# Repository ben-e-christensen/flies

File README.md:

# FLIES — electrometer + camera acquisition and analysis

Scripts for the FLIES charging experiments in the Burton Lab. A Keithley 6514
electrometer logs charge (or current/voltage) over serial while FLIR
Grasshopper3 and/or Logitech Brio 101 cameras record the sample. An Arduino
relay switches two lamps (A = "going into Faraday cage", B = "going into
acrylic"). When the signal "blips", the scripts save a camera burst around it.
The other scripts plot, review, turn into video, and compress the resulting
session folders.

Split out of [burtonlab](https://github.com/ben-e-christensen/burtonlab)
(`flies/` folder) with its git history kept.

## Setup

```bash
python -m venv .venv
.venv\Scripts\activate
pip install numpy matplotlib opencv-python pyserial pillow pandas
```

You also need:

- **PySpin** (Spinnaker SDK) for the FLIR camera. Install the wheel that
  matches your Python version from Teledyne FLIR's site. This is why the old
  `.venv312` existed.
- **ffmpeg / ffprobe** for the Brio capture, the video scripts and the
  compressor. Several scripts hard-code an `FFMPEG = r'...'` path in their
  CONFIG block, so check it.
- Set the instrument serial ports in **`coms.py`**.

Most scripts have a `# ============ CONFIG ============` block at the top, and
many default to paths like `E:\Ben Christensen\FLIES\...`. Edit it before you
run a script, or pass a session folder on the command line.

## A session folder

The acquisition scripts write one folder per run:

```
session_<YYYY-MM-DD_HH-MM-SS>/
    meta.txt                 key<TAB>value settings (cap_F, fps, ports, wall_clock_start ...)
    electrometer.csv         time,charge,trigger  |  time,voltage_V,trigger (voltage mode)
    events.csv               one row per blip / manual save (event,time,lamp,...)
    lamps.csv                lamp state over time (newer sessions only)
    flir/e001_0000.png ...   FLIR burst frames for event 1 (16-bit PNG)
    flir_frames.csv          time,event,filename
    brio1/e001_0000.jpg ...  Brio burst frames (+ brio1_frames.csv)
    *_cont/p003_000000.*     continuous frames during lamp phase 3 (some modes)
    analysis/                written by the analysis scripts
```

All timestamps are seconds since the Start button, on one shared clock, so the
CSVs line up with each other.

---

## Top-level files

### Shared config

| File | What it does |
|---|---|
| `coms.py` | The one place for serial ports. `port('keithley')` / `port('arduino')` returns the right `COMx` on Windows or `/dev/tty*` on Linux. Every acquisition script imports it. |

### Acquisition (Tkinter GUIs: live plot, lamp buttons, Start/Stop)

| File | What it does |
|---|---|
| `main.py` | Charge-mode Keithley + **one FLIR**, with automated lamps. Start runs the cycle: lamp A on → wait for a charge blip → lamp stays on 30 s → dark → lamp B → … . The FLIR keeps a RAM ring buffer and writes it to disk only when a blip fires, so each burst includes the lead-in. Pressing a manual lamp button turns the automation off. (The docstring still says "UNTESTED", but the commit history says it has been tested.) |
| `main_untested.py` | Same automation with **two FLIRs**. Only the camera opposite the lit lamp caches. The blip rule is a swing in either direction, and each burst includes 15 s of post-roll after the blip. |
| `main_test.py` | Dual-FLIR version from `main_untested.py`, plus **continuous 20 fps saving** from camera A while one lamp (`CONT_LAMP`) is on. Frames go to `flir_a_cont/p###_######.png` through a bounded writer pool. When the disk can't keep up, frames are dropped and counted so RAM doesn't fill. |
| `main_voltage.py` | The newest and largest version. The Keithley runs in **voltage mode** across a 1 nF cap (1 mV = 1 pC), with one FLIR (PySpin) and two Brio 101s (read through ffmpeg for real MJPG). Each lamp has its own settings for which cameras cache and which save continuously. It adds an "Auto trigger" toggle and a "Save burst" button (or the M key). Writes to `E:\Ben Christensen\FLIES\session_*`. |

### Session analysis and plotting

| File | What it does |
|---|---|
| `plot_main.py` | Plots charge for a whole session (`electrometer.csv`). Events show as dashed lines and FLIR burst spans as cyan bands. Saves `session_charge.png`. Works with charge-mode and voltage-mode data (Q = C·V, with C from `meta.txt`). |
| `plot_blips.py` | One plot per event, covering ±30 s around the blip. A second x-axis shows FLIR frame numbers and shades the burst span. |
| `session_overview.py` | Whole-session overview plus one plot per **episode** (events close together are merged). Colors come from the lamp state logged in `events.csv` / `lamps.csv`. Writes `analysis/overview/`. Pass a session folder, or the FLIES folder to process every session. |
| `session_overview_multiple.py` | One long charge plot across several sessions or folders, ordered by `wall_clock_start`. Sessions are either laid end to end or placed at their real clock times. Writes PNG, SVG (for Inkscape) and a sessions CSV. |
| `logger.py` | Despite the name, this is the interactive **blip viewer**. It shows the session trace, a zoom on the current event, and the Brio frame nearest the cursor. Events come from `events.csv`, your own `EXTRA_TIMES` and optional offline detection. Keyboard controls: n/p for events, arrow keys to step frames, space to play, s to take a snapshot, e to export. `--export` writes summary PNGs without opening the window. |

### Video making

| File | What it does |
|---|---|
| `flir_video.py` | Makes one MP4 per event from the FLIR burst frames (`e001_*.png` …), with the 16-bit frames scaled to 8-bit. |
| `video_and_charge.py` | Event video. Every camera that recorded the event is on top (FLIR, brio1, brio2), and the charge trace draws itself in underneath. The FLIR sets the clock. The other cameras show their latest frame at or before that time, labeled with the offset. Also writes a `_sync.csv` that maps each video frame to its source files. |
| `video_cont.py` | Same as `video_and_charge.py`, for sessions where the Brios saved **continuous** frames (`brio*_cont/`) instead of bursts. |
| `triple.py` | An older 3-panel version for one FLIR + one Brio: FLIR burst, Brio burst and charge trace side by side, with a sync CSV. |
| `trying.py` | Side-by-side clip of Brio continuous frames and a charge trace that draws itself in, for frame ranges you list in `CLIPS` (e.g. `p002_001550` → `p002_001560`). Supports slow motion. |

### Frame quality check

| File | What it does |
|---|---|
| `fly_finder.py` | Scans every continuous FLIR frame (`flir_a_cont/p###_######.png`) and compares it with a reference frame using mean diff, fraction of changed pixels, sharpness and brightness. It flags robust outliers. The scan can resume where it stopped. Writes `scores.csv`, `flagged.csv`, a plot and copies of flagged frames to `frame_check/`. |
| `flag.py` | Summarizes the results from `fly_finder.py`: counts by reason, by session and lamp phase, runs of consecutive flagged frames, the most extreme frames, and missing files. It can copy the worst N frames per metric so you can look through them. |
| `prune.py` | One-off: removes rows at or before a given reference frame from `scores.csv`, plus rows whose files no longer exist. Keeps a `.bak` copy. The paths are hard-coded. |

### Data transfer

| File | What it does |
|---|---|
| `compress.py` | Copies a FLIES folder for transfer, turning each image sequence into one video (H.264, or FFV1 for exact 16-bit) with a per-frame manifest CSV. Other files are copied as-is, and the source folder is never modified. Frame counts are checked with ffprobe, and the script can resume. `--restore` / `--extract` decode videos back into the original frame files. |
| `compress_v2.py` | `compress.py` plus lock files so several runs can go at once, and `--skip-cont`, `--only-cont` and `--reverse` for ordering. Each run writes its own log. |

---

## `other_modes/` — earlier acquisition variants

These put the repo root on `sys.path` so they can import `coms`. Output goes to
`other_modes/Kiethley_data/`.

| File | What it does |
|---|---|
| `main.py` | Minimal GUI: Keithley in **charge** mode, live scrolling plot, CSV log. No cameras, no relay. |
| `main_ubuntu.py` | The same minimal GUI in **current** mode (nA), with serial auto-detection for Linux `/dev/ttyUSB*` / `ttyACM*`. |
| `main_test.py` | Charge mode + **two Brio 101s** captured through ffmpeg (real MJPG). JPEGs are written as received, with no re-encode. |
| `main_current.py` | **Current** mode + two Brios (ffmpeg) + FLIR (PySpin). Charge is recovered afterwards by integrating the current. |
| `main_voltage.py` | **Voltage** mode across an RC network (R = 5.15 MΩ, C = 93.4 nF), with charge computed live as Q = C·V. Two Brios through OpenCV + FLIR. |
| `Kiethley_data/electrometer_2026-09-01_17-08-18.csv` | A small sample charge log (`time,charge` in coulombs). |

## `test_scripts/` — hardware tests and early prototypes

| File | What it does |
|---|---|
| `cam_test.py` | Opens one webcam with OpenCV/DSHOW and shows it live. q quits. |
| `cam_test_v2.py` | Records two Brios with ffmpeg and a live preview. SPACE starts or stops recording. `list` shows the dshow device names. |
| `pair_test.py` | Measures the real fps of two cameras by counting only frames whose content changed, because `grab()` on DSHOW returns True even when no new frame arrived. |
| `electro.py` | Headless Keithley charge logging for `DURATION_S` seconds, then a plot. No GUI. |
| `integrate.py` | Integrates a current-mode `electrometer.csv` (trapezoid rule) into charge. Writes `charge_integrated.csv` and a two-panel plot. |
| `integrated.py` | Early GUI: Keithley charge + two OpenCV webcams. |
| `old_main.py` | Earlier current-mode Keithley + two Brios (OpenCV) + FLIR logger, with charge integrated live. |
| `main_arduino.py` | `old_main.py` plus Arduino relay control of the lamps. `main.py` at the top level was built from this. |
| `main_no_cam.py` | Keithley charge mode + Arduino relay buttons, no cameras. |
| `plot_main.py` | Plots a single `electrometer.csv` (charge in pC). By default it uses the newest one. |
| `plot_blocks.py` | Splits a charge log at `SPLIT_TIMES` into labeled blocks (Idle / Fan On / Beads In …). Each block gets its own plot, an optional fit, and optional 10 s zoom windows. |
| `spike_review.py` | Finds charge spikes (|dq/dt| outliers) in a time window, copies the camera frames around each one and makes a movie of the block. |
| `make_clip.py` | Makes an MP4 of cam0/cam1 frames between `CLIP_START` and `CLIP_END`, per camera and side by side. |
| `identity_test.png` | Test image. |

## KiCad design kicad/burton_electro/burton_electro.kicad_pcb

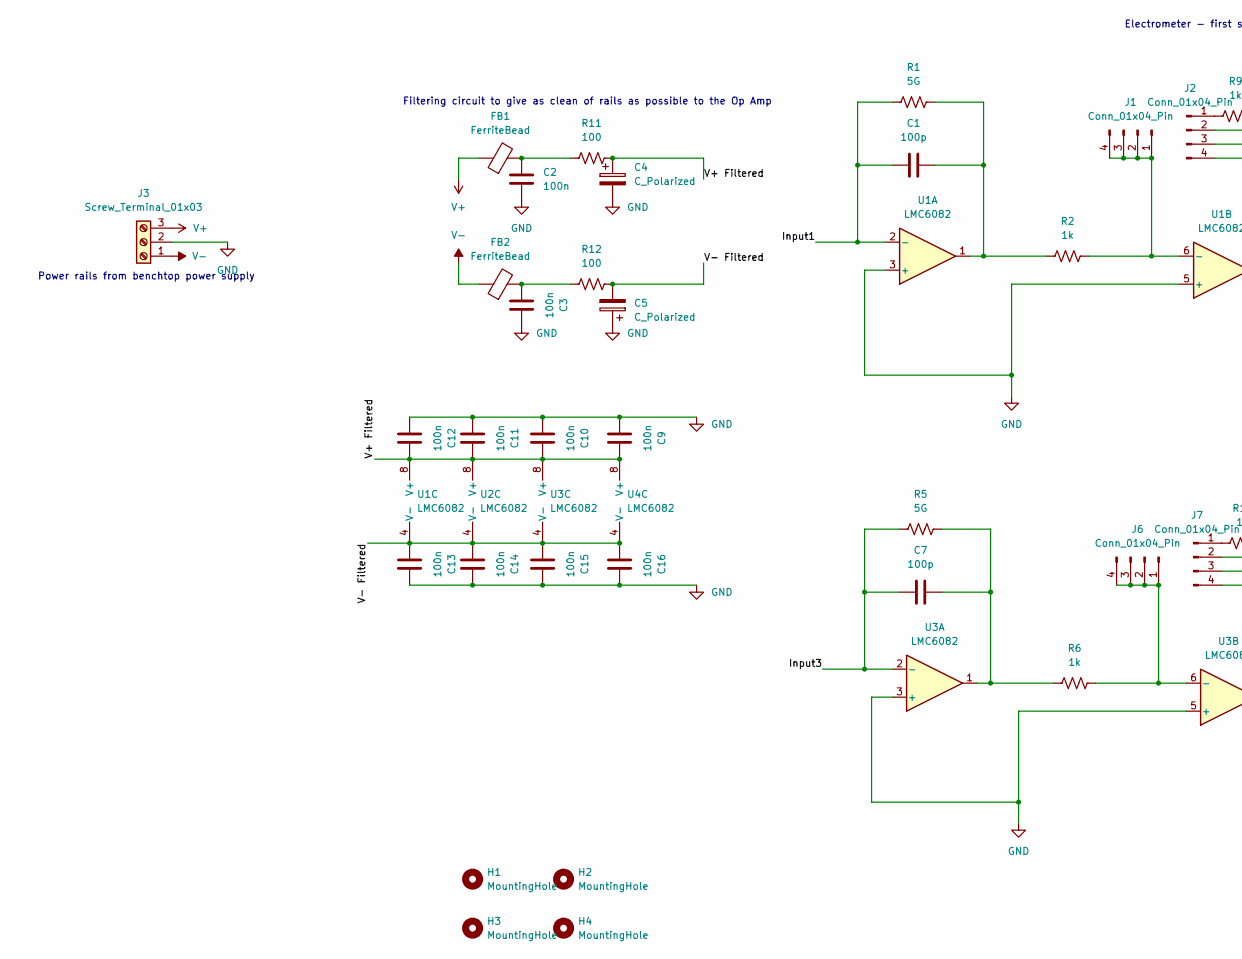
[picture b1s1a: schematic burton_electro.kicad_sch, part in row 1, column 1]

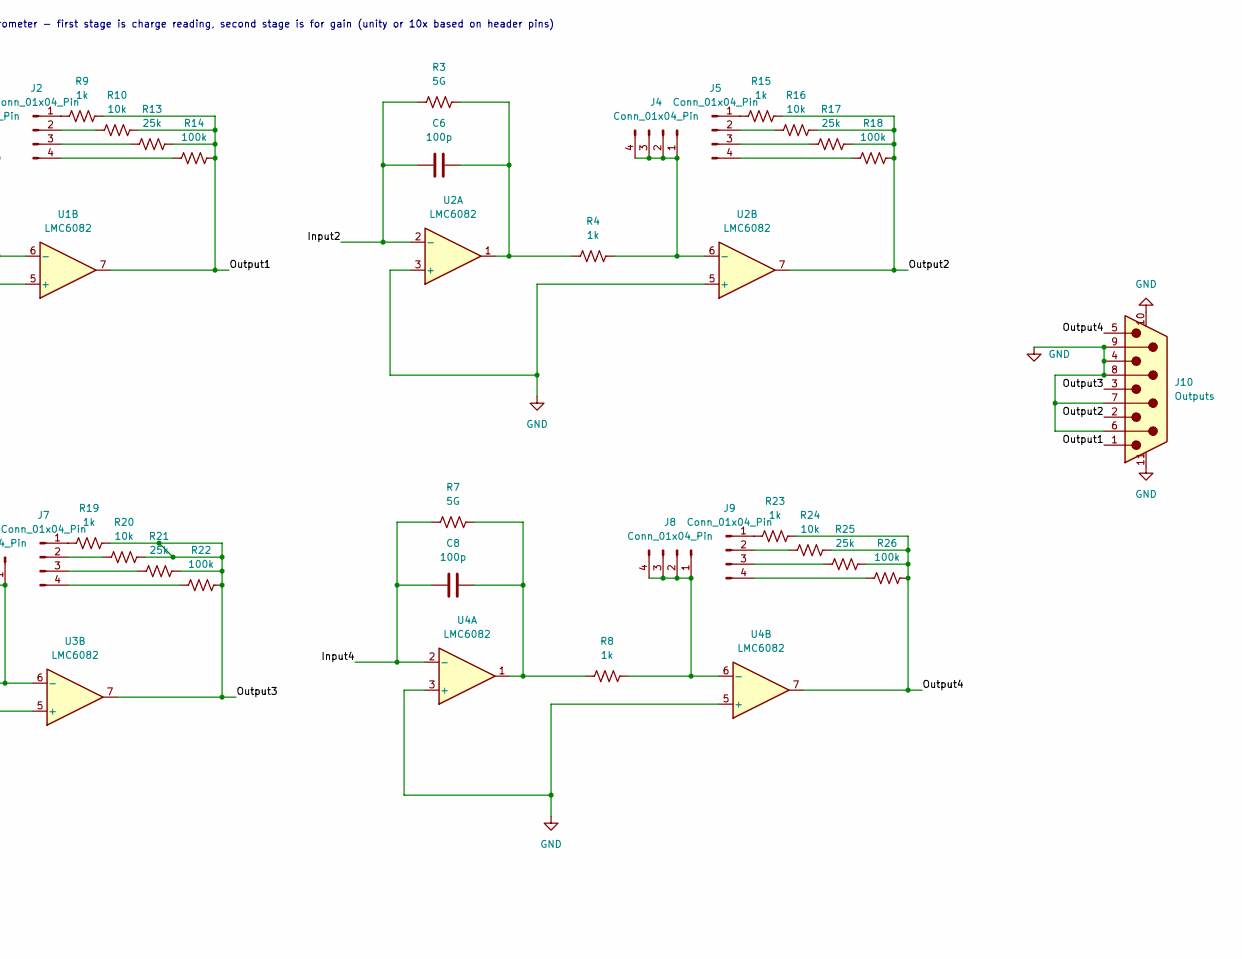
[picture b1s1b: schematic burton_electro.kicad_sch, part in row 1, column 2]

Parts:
C1, C6, C7, C8: 100p; C_Disc_D3.0mm_W1.6mm_P2.50mm
C2, C3, C9, C10, C11, C12, C13, C14, C15, C16: 100n; C_0805_2012Metric_Pad1.18x1.45mm_HandSolder
C4, C5: C_Polarized; CP_Elec_10x10.5
FB1, FB2: FerriteBead; L_1206_3216Metric
H1, H2, H3, H4: MountingHole; MountingHole_2.7mm
J1, J2, J4, J5, J6, J7, J8, J9: Conn_01x04_Pin; PinHeader_1x04_P2.54mm_Vertical
J3: Screw_Terminal_01x03; Altech_AK100_1x03_P5.00mm
J10: Outputs; DSUB-9_Pins_Horizontal_P2.77x2.84mm_EdgePinOffset7.70mm_Hou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
R1, R3, R5, R7: 5G; R_Axial_DIN0204_L3.6mm_D1.6mm_P2.54mm_Vertical
R2, R4, R6, R8, R9, R15, R19, R23: 1k; R_0805_2012Metric_Pad1.20x1.40mm_HandSolder
R10, R16, R20, R24: 10k; R_0805_2012Metric_Pad1.20x1.40mm_HandSolder
R11, R12: 100; R_0805_2012Metric_Pad1.20x1.40mm_HandSolder
R13, R17, R21, R25: 25k; R_0805_2012Metric_Pad1.20x1.40mm_HandSolder
R14, R18, R22, R26: 100k; R_0805_2012Metric_Pad1.20x1.40mm_HandSolder
U1, U2, U3, U4: LMC6082; DIP-8_W7.62mm

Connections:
/Input1: C1.1, R1.1, U1.2 (-)
/Input2: C6.1, R3.1, U2.2 (-)
/Input3: C7.1, R5.1, U3.2 (-)
/Input4: C8.1, R7.1, U4.2 (-)
/Output1: J10.1, R9.2, R10.2, R13.2, R14.2, U1.7
/Output2: J10.2, R15.2, R16.2, R17.2, R18.2, U2.7
/Output3: J10.3, R19.2, R20.2, R21.2, R22.2, U3.7
/Output4: J10.5, R23.2, R24.2, R25.2, R26.2, U4.7
/V+ Filtered: C4.1, C9.2, C10.2, C11.2, C12.2, R11.2, U1.8 (V+), U2.8 (V+), U3.8 (V+), U4.8 (V+)
/V- Filtered: C5.2, C13.1, C14.1, C15.1, C16.1, R12.2, U1.4 (V-), U2.4 (V-), U3.4 (V-), U4.4 (V-)
GND: C2.1, C3.2, C4.2, C5.1, C9.1, C10.1, C11.1, C12.1, C13.2, C14.2, C15.2, C16.2, J3.2, J10.4, J10.6, J10.7, J10.8, J10.9, J10.10, J10.11, J10.SH, U1.3 (+), U1.5 (+), U2.3 (+), U2.5 (+), U3.3 (+), U3.5 (+), U4.3 (+), U4.5 (+)
unnamed: C1.2, R1.2, R2.1, U1.1
unnamed: C2.2, FB1.2, R11.1
unnamed: C3.1, FB2.2, R12.1
unnamed: C6.2, R3.2, R4.1, U2.1
unnamed: C7.2, R5.2, R6.1, U3.1
unnamed: C8.2, R7.2, R8.1, U4.1
unnamed: J1.1, J1.2, J1.3, J1.4, R2.2, U1.6 (-)
unnamed: J2.1, R9.1
unnamed: J2.2, R10.1
unnamed: J2.3, R13.1
unnamed: J2.4, R14.1
unnamed: J4.1, J4.2, J4.3, J4.4, R4.2, U2.6 (-)
unnamed: J5.1, R15.1
unnamed: J5.2, R16.1
unnamed: J5.3, R17.1
unnamed: J5.4, R18.1
unnamed: J6.1, J6.2, J6.3, J6.4, R6.2, U3.6 (-)
unnamed: J7.1, R19.1
unnamed: J7.2, R20.1
unnamed: J7.3, R21.1
unnamed: J7.4, R22.1
unnamed: J8.1, J8.2, J8.3, J8.4, R8.2, U4.6 (-)
unnamed: J9.1, R23.1
unnamed: J9.2, R24.1
unnamed: J9.3, R25.1
unnamed: J9.4, R26.1
V+: FB1.1, J3.3
V-: FB2.1, J3.1

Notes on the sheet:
Electrometer - first stage is charge reading, second stage is for gain (unity or 10x based on header pins)
Power rails from benchtop power supply
Filtering circuit to give as clean of rails as possible to the Op Amp

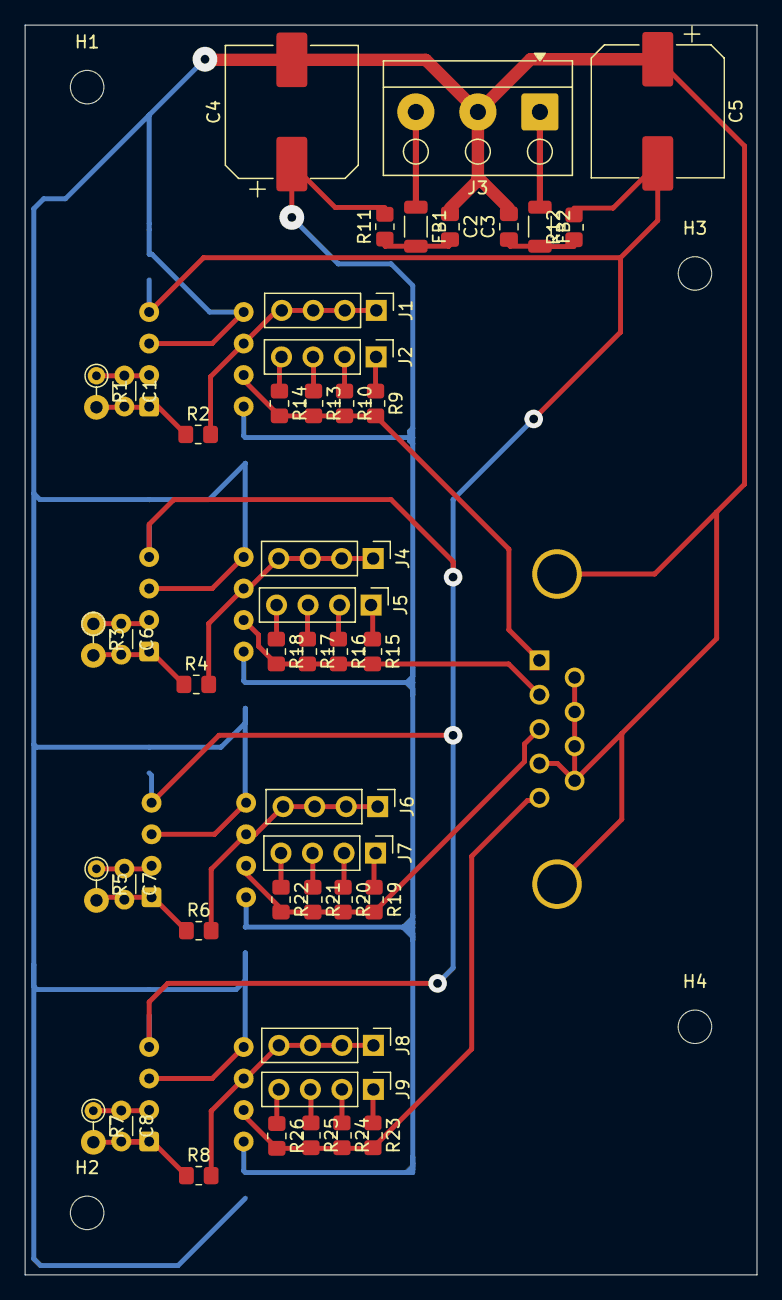
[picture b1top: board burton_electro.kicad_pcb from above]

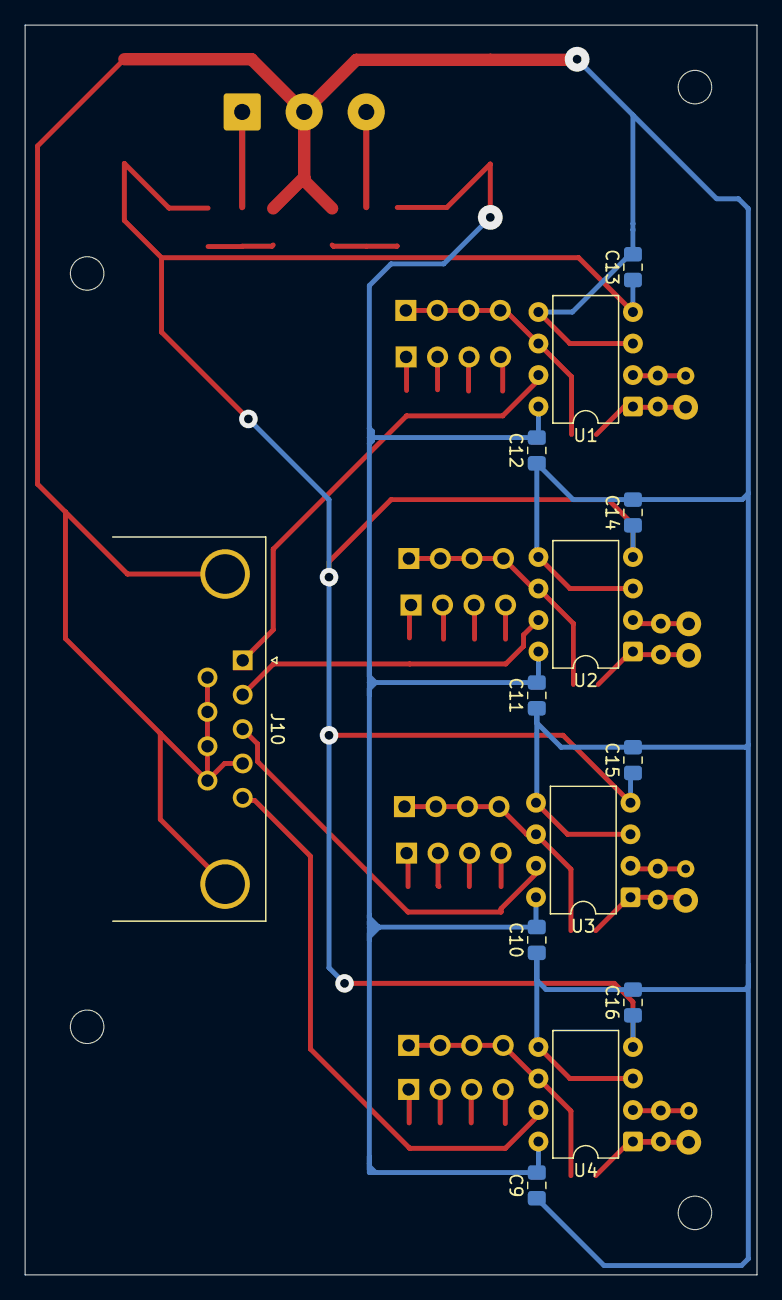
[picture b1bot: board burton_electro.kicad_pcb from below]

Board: 2 copper layers, 59.0 x 100.8 mm, 62 parts (13 on the bottom side), 39 nets.

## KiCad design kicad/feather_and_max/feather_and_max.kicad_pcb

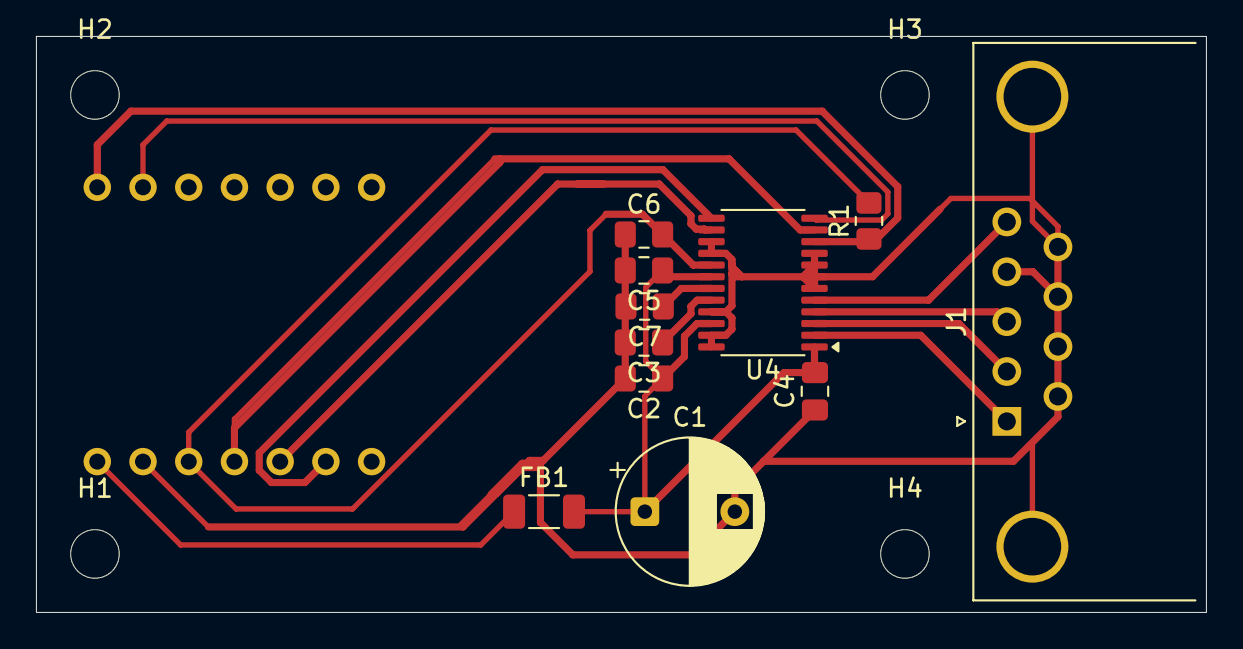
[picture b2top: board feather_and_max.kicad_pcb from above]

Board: 2 copper layers, 65.0 x 32.0 mm, 16 parts (1 on the bottom side), 15 nets.

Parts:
C1: 10uF; CP_Radial_D8.0mm_P5.00mm
C2, C4, C5, C6, C7: 100nF; C_0805_2012Metric_Pad1.18x1.45mm_HandSolder
C3: 1uF; C_0805_2012Metric_Pad1.18x1.45mm_HandSolder
FB1: FerriteBead; L_1206_3216Metric_Pad1.22x1.90mm_HandSolder
H1, H2, H3, H4: MountingHole; MountingHole_2.7mm
J1: electros; DSUB-9_Pins_Horizontal_P2.77x2.84mm_EdgePinOffset7.70mm_Hou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
R1: 10k; R_0805_2012Metric_Pad1.20x1.40mm_HandSolder
U1: XIAO ESP32C3; XIAO-ESP32-C6-DIP
U4: MAX1032BEUG_; TSSOP-24_4.4x7.8mm_P0.65mm

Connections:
+3.3V: C6.2, R1.2, U1.12 (VCC_3V3), U4.17 (DVDD0)
+5V: FB1.1, U1.14 (VUSB)
/5V Filt: C1.1, C2.1, C4.2, C5.1, FB1.2, U4.1 (AVDD1), U4.18 (DVDD), U4.22 (AVDD2)
/CS: R1.1, U1.1 (D0), U4.10 (~CS)
/Electro1: J1.1, U4.2 (CH0)
/Electro2: J1.2, U4.3 (CH1)
/Electro3: J1.3, U4.4 (CH2)
/Electro4: J1.5, U4.5 (CH3)
/MISO: U1.10 (D9), U4.14 (DOUT)
/MOSI: U1.11 (D10), U4.11 (DIN)
/SCLK: U1.9 (D8), U4.13 (SCLK)
/SSTRB: U1.2 (D1), U4.12 (SSTRB)
GND: C1.2, C2.2, C3.2, C4.1, C5.2, C6.1, C7.2, J1.4, J1.6, J1.7, J1.8, J1.9, J1.SH, U1.13 (GND), U4.6 (CH4), U4.7 (CH5), U4.8 (CH6), U4.9 (CH7), U4.15 (DGND0), U4.16 (DGND), U4.21 (AGND3), U4.23 (AGND2), U4.24 (AGND1)
unnamed: C3.1, U4.20 (REF)
unnamed: C7.1, U4.19 (REFCAP)
